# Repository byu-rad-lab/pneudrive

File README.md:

# PneuDrive Pressure Control System

This repository contains all of the designs, code, and instructions needed to create a low level pressure controller designed for pneumatically actuated robots. This pressure controller is designed to use relatively inexpensive off-the-shelf components and to favor simplicity in an effort to make it easy to understand and adapt for different applications.

Here is a [video](https://bit.ly/3QkrEqO) that is a brief overview of the system.

<!-- add picture of boards from resources folder -->

The pressure control system consists of one single-board-computer (SBC) acting as the ROS master and communicating serially with one or more Arduinos. The SBC needs to be capable of running ROS/Ubuntu (e.g. Raspberry Pi, NVIDIA Jetson, Odroid). We use the [ODROID N2+](https://www.hardkernel.com/shop/odroid-n2-with-4gbyte-ram-2/). We also provide python bindings that allow you to interact with the pressure controller without ROS.

Each Arduino performs high-rate (~1 kHz) pressure control of up to 4 chambers and transmits pressure data back to the ROS master. A high level diagram of the pressure control system can be seen in the figure below:

## Dependencies

## Installation
If the SBC is connected to the internet, the easiest way to use PneuDrive is to clone the repository directly onto the SBC. If the SBC is not connected to the internet, you can clone the repository onto another computer and then copy it over to the SBC using a tool like scp over a local network:

``` console
scp -r <path to pneudrive on computer> <username@SBC_IP_ADDRESS>:<path to desired location on SBC>
```

If you intend to use PneuDrive with ROS, just make sure the package is placed into the src directory of a ROS workspace. Once the pneudrive package in in the src directory, you can build it using ```colcon build``` from the root of the workspace.

If you intend to use PneuDrive without ROS (i.e. using the python bindings), you can place the package anywhere on the SBC. Python bindings are implemented using pybind11, so when cloning the repository, it is important to pass ```--recurse-submodules``` to git to ensure that pybind11 is cloned as well:

``` console
git clone --recurse-submodules <git url>
```

To build the bindings, you will just need to navigate to the python_bindings directory and build the bindings manually with cmake:

``` console
cd python_bindings
mkdir build
cd build
cmake ..
make
```

## How is it organized

This repository is structured as a ROS package. It is designed to be placed in a ROS workspace on the SBC used for pressure control. There are however several other directories not necessary for a ROS package:

* **pcb_design** - this directory contains all of the wiring diagrams and PCB schematics. Instructions for the population of the PCB as well as wiring the entire pressure controller are found here.
* **odroid_setup** - this directory contains all of instructions and files necessary to set up an ODROID for use as the ROS master in a pressure control system.
* **arduino_firmware** - this directory contains the instructions and code needed to program the arduinos to act as high rate pressure controllers.
* **python_bindings** - this directory contains python bindings to interact with PneuDrive independent of ROS, in a python scripting environment.

## Steps to create a pressure control system

1. Use the instructions and schematics in the **pcb_design** directory to order and assemble the necessary components to construct a PneuDrive controller PCB and several embedded PCBs.
2. Use the instructions and files in the **odroid_setup** directory to setup the SBC as the ROS master
3. Use the instructions and files in the **arduino_firmware** directory to program each arduino as a high-rate pressure controller

## Running the PneuDrive ROS Node

Once the SBC boots up it you can ssh into it with ```ssh ubuntu@192.168.0.xxx```. The username is ```ubuntu``` and the password is ```temppwd```. This process might be slightly different depending on your SBC.

Once you are logged in, you can launch the pressure control ROS node (along with a roscore) using the following command:

``` shell
ros2 launch pneudrive rs485_pressure.launch.py numjoints:=[number of joints]
```

where the ```numjoints``` command line argument is required and tells the node how many joints to look for on the serial bus. 

This creates a ROS node called "PressureController". Depending on ```numjoints```, the node will create addresses for each joint. The node then creates publishers and subscribers for every joint specified by the addresses. If the SBC cannot find all of the specified addresses, the node throw an error and shut down. If this happens, here are some common fixes:

* Make sure your wires are all connected securely and correctly.
* Make sure that each pressure control board dip switch is set to the proper address. The dip switch positions are printed on the pcb and they should match what is specified in the yaml file. For example, if I have a 3 joint arm, I would make sure that the first joint is set to 0 then the next as 1 and the last as 2, with those same addresses specified in the code. 
* Make sure you didn't flip the A+ and B- wires when wiring up the connectors. We chose to use screw terminals for ease of use, but this does make flipping wires easier if you aren't being careful. 

When the node launches, it will print out all of the joints it detected and start the node.

## Citation

If you use PneuDrive in your research, please cite the our paper:

```bibtex

 @inproceedings{
	 Johnson_Cheney_Cordon_Killpack_2024, 
	 address={San Diego, CA, USA}, 
	 title={PneuDrive: An Embedded Pressure Control System and Modeling Toolkit for Large-Scale Soft Robots}, 
	 rights={https://doi.org/10.15223/policy-029}, 
	 ISBN={9798350381818}, 
	 url={https://ieeexplore.ieee.org/document/10521958/}, 
	 DOI={10.1109/RoboSoft60065.2024.10521958}, 
	 booktitle={2024 IEEE 7th International Conference on Soft Robotics (RoboSoft)}, 
	 publisher={IEEE}, 
	 author={Johnson, Curtis C. and Cheney, Daniel G. and Cordon, Dallin L. and Killpack, Marc D.}, 
	 year={2024}, 
	 month=apr, 
	 pages={786–792}, 
	 language={en} 
 }

```

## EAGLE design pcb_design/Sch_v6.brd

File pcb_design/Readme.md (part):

# Overview

This project was made by members of the Robotics and Dynamics Lab at Brigham Young University. This directory contains all of the necessary instructions and files for the custom PCB we designed to implement pressure control for 4 different pressure chambers. This board, in combination with our beaglebone black cape, enables the use of ROS to send and receive pressure data/commands to the lower level controller located on the arduino.

These PCBs were designed using Autodesk EAGLE. The corresponding project, board, and schematic files are found in this directory, as well as the CAM outputs.

We used OSHPARK to print out PCBs. For convenience, their design rules are also included in this repo. To use them, navigate to 'Design Rules' in Eagle and click load to select the .dru file. This will load OSHPARK's manufacturing rules automatically for design rule checking.

We have also created a custom part library which includes footprints, schematics, and 3d models for each major component used in this design. To use the library, simply add the filepath of the .lbr file to Eagle's search path in the Control Panel. For more info see [here](https://www.instructables.com/Adding-a-Library-to-Eagle-CAD/).

There are two pcbs in this directory: a beaglebone black cape and the pressure control board.

Here are some renderings of the pressure control pcb:

---
# Pressure Control Board

## Bill of Materials for each Board

| Qty |  Cost  | Value                           | Device                          | Parts                                                   | Description                                 | PURCHASE_URL |
|-----|--------|---------------------------------|---------------------------------|---------------------------------------------------------|---------------------------------------------|--------------|
| 8   | $2.00  | 100nF                           | CERAMIC_CAPACITOR               | C5, C6, C7, C8, C9, C10, C11, C12                       | Ceramic capacitors for filtering            | [link](https://www.digikey.com/en/products/detail/kemet/C315C102K1R5TA7301/6562324)         |
| 4   | $1.04  | 12k                             | R-US_0204/7                     | R1, R2, R3, R4                                          | RESISTOR, American symbol                   | [link](https://www.digikey.com/en/products/detail/vishay-beyschlag-draloric-bc-components/MBB02070C1202FCT00/7351022)          |
| 4   |  $.96  | 1nF (0.1uF)                     | CERAMIC_CAPACITOR               | C1, C2, C3, C4                                          | Ceramic capacitors                          | [link](https://www.digikey.com/en/products/detail/kemet/C322C104K5R5TA7301/3726048)             |
| 1   |  $.46  | 2PIN_DIP_DS01-254-S-02BE        | 2PIN_DIP_SWITCH                 | I2C_SEL                                                 | Dip switch for selecting i2c address        | [link](https://www.digikey.com/en/products/detail/cui-devices/DS01-254-S-02BE/11310829)             |
| 2   |  $.28  | 4.7k                            | R-US_0204/7                     | R5, R6                                                  | RESISTOR, American symbol                   | [link](https://www.digikey.com/en/products/detail/vishay-beyschlag-draloric-bc-components/SFR2500004701FR500/333920)           |
| 2   | $11.90 | A4990_DUAL_MOTOR_DRIVER_CARRIER | A4990_DUAL_MOTOR_DRIVER_CARRIER | DRIVER_A, DRIVER_B                                      | A4990 Dual Motor Driver Carrier (Pololu)    | [link](https://www.pololu.com/product/2137/)              |
| 1   | $10.90 | ARDUINO_NANO_EVERY              | ARDUINO_NANO_EVERY              | NANO1                                                   | Arduino Nano Every                          | [single](https://store.arduino.cc/usa/nano-every) or [pack](https://store.arduino.cc/usa/nano-every-pack)             |
| 7   | $8.70  | PHOENIX_CONTACT_1759017         | PHOENIX_CONTACT_1759017         | 12V_IN, I2C_IN, I2C_OUT, VALVE0, VALVE1, VALVE2, VALVE3 | Crimpless connections for peripherals       | [female](https://www.digikey.com/en/products/detail/phoenix-contact/1759017/260463), [male](https://www.digikey.com/en/products/detail/phoenix-contact/1757019/260379), or [set](https://www.amazon.com/Willwin-Pitch-Pluggable-Terminal-Connectors/dp/B077GTYZVM/ref=sr_1_15?dchild=1&keywords=PCB%2BMount%2BScrew%2BTerminal%2BBlock%2C%2Bright%2Banlge%2BPlug-in%2B2-Pin%2B(2%2BPole)%2BScrew%2BTerminal%2BBlock%2BConnector%2C%2BPluggable%2BMale%2BFemale%2BPhoenix%2BType%2BConnector&qid=1619925723&s=hi&sr=1-15&th=1)             |
| 4   | $76.84 | PRESSURE_SENSOR_ABPDRNN100PGAA5 | PRESSURE_SENSOR_ABPDRNN100PGAA5 | PS0, PS1, PS2, PS3                                      | Honeywell Pressure Sensor (ABPDRNN100PGAA5) | [link](https://www.mouser.com/ProductDetail/Honeywell/ABPDRNN100PGAA5?qs=sGAEpiMZZMvhQj7WZhFIAD2P7qVC0dZ7tI11ZYAVyGqQk%2FMhVJdgGw%3D%3D)             |

NOTE: We want our pcb to be easy to service if things break. So instead of soldering parts directly to the pcb, we use [female headers](https://www.amazon.com/Qunqi-2-54mm-Straight-Connector-Arduino/dp/B07CGGSDWF/ref=sr_1_3?dchild=1&keywords=female+header+pins&qid=1587769954&sr=8-3) to plug the arduino and motor drivers in so that they can be replaced easily.

The total price per board (including printing the pcb) is about $150 (parts are $113.08 and Oshpark charges about $40 for 3 copies of the pcb). Note that there are farily significant bulk discounts for many of these parts. 

## Schematic

## Specifications and Design Notes
### I2C Design
The I2C bus on this pcb has both an IN and OUT port. The OUT port is useful for daisy chaining multiple of these pcbs, but is not required. The arduino communicates on a 5V logic level, which is incompatible with the 3.3V logic of the BBB. To remedy this, we use a bi-directional logic level shifter to make sure voltages are at the right levels for each device. The shifter is used once on the BBB cape and outputs 5V to any arudino board down the line. The logic shifter uses 10k pullup resistors on the SDA and SCL lines. According to [this](https://www.ti.com/lit/an/slva689/slva689.pdf?ts=1612978067135&ref_url=https%253A%252F%252Fwww.google.com%252F) resource, 10k is too high for our I2C line. 

The max for I2C fast mode is 400 pF according to Table 1. Since we don't have that many devices and the wires aren't super long, we assumed a bus capacitance of about 150pF. This combined with the operating voltage of 5V on fast mode gives a minimum resistance value of about 1.5k (from Fig 2) and a max resistance of about 2.5k 9 (from Fig 3). In order to get an equivalent resistance in this range with the 10k resistors in the logic shifter, we add a 2.2k resistor in parallel to get an equivalent pullup resistance of 1.8k. We measured the performance of the I2C bus with these resistors in place and observed about 380-390Hz bit rate (the 10k resistors alone work, but the bit rate was ~340Hz and the voltage level was barely reaching high). The closer the equivalent resistance is to the minimum resistance, the faster the line can transfer data at the cost of higher power consumption. 

### PCB Design Notes

* Trace widths on the board are mostly the default that eagle uses with a few exceptions. The 12V line is 80mils wide and the 5V line is 30 mils wide. The trace for the 12V line was made as as large as possible because it is a high current line. Each 2 phase driver board can deliver 0.7 amps/phase, which gives a total continuous current of up to 2.8A on each board. The driver boards can go up to 0.9A/phase, but not for long. Using [this](https://www.digikey.com/en/resources/conversion-calculators/conversion-calculator-pcb-trace-width) trace width calculator tool (with 2.8A, 1oz/ft^2, and an ambient temp of 25C) gives us an acceptably low temperature rise (5-10C) for an external trace.

* There are two ground planes in this PCB. The top plane is for the signal ground and the bottom plane is the motor power ground. This was done in an attempt to minimize noise from the motors on the analog pressure sensors. These ground are connected through the GND pins on the driver boards so that the both ground planes are connected to each other when it is running. But by only connecting the ground planes through the driver boards, it encourages any noisy currents to follow the path of least impedance (the ground plane) back to source instead of going through the signal ground. We used [this](https://www.nxp.com/docs/en/application-note/AN1259.pdf) and [this](https://electronics.stackexchange.com/questions/112508/ground-vs-power-ground) as resources as to why we chose to do this. We also did our best to separate the two areas of the board (i.e. the drivers from the pressure sensors) as much as possible without making the board too big. 

* The mounting holes are designed for M3 screws.

## Board and CAD File

See [here](https://a360.co/3wIiBnY) to see the 3d version of the board. You can download the included step file too if you want to design a case, for example.

## Things to consider for a future revision of the board

* Find a robust way to plug the pressure sensors into the board. Right now they're soldered directly to the board, but it would be convenient to be able to unplug and replace them.
* Do something with the EF pins on the driver boards. Right now they are connected to the arduino, but not doing anything with them. 
* We are using shielded cable for the i2c bus. Technically, the cable shield should be grounded somewhere. It isn't currently. Could add a screw terminal to the board to ground the bare ground wire possibly.

---
# Beaglebone Black Cape

## Bill of Materials

| Qty | Cost  | Value                      | Device                     | Package                 | Parts                                        | Description                                   | Purchase Link                                                                                                                                                                                                                                                                                                                                                                                                                                             |
|-----|-------|----------------------------|----------------------------|-------------------------|----------------------------------------------|-----------------------------------------------|-----------------------------------------------------------------------------------------------------------------------------------------------------------------------------------------------------------------------------------------------------------------------------------------------------------------------------------------------------------------------------------------------------------------------------------------------------------|
| 4   |       | 2.2k                       | R-US_0204/7                | 0204/7                  | R1, R2, R3, R4                               | RESISTOR, American symbol                     |                                                                                                                                                                                                                                                                                                                                                                                                                                                           |
| 5   | $8.70 | PHOENIX_CONTACT_1758018    | PHOENIX_CONTACT_1758018    | PHOENIX_CONTACT_1758018 | GND, I2C1_OUT, I2C2_OUT, PWR_BUT, PWR_ENABLE | Crimpless peripheral connections              | [female](https://www.digikey.com/en/products/detail/phoenix-contact/1758018/260496), [male](https://www.digikey.com/en/products/detail/phoenix-contact/1757019/260379), or [set](https://www.amazon.com/Willwin-2-Pin-5-08mm-Female-Terminal/dp/B077979RZR/ref=pd_di_sccai_3?pd_rd_w=A5pho&pf_rd_p=c9443270-b914-4430-a90b-72e3e7e784e0&pf_rd_r=5PEX8D4W251F0MR04JT6&pd_rd_r=e4559510-59fe-4a1b-9aaf-c49878303df9&pd_rd_wg=2cx5U&pd_rd_i=B077979RZR&th=1) |
| 1   | $2.50 | POLOLU_LOGIC_SHIFTERPOLOLU | POLOLU_LOGIC_SHIFTERPOLOLU | POLOLU_LOGIC_SHIFTER    | SHIFTER1                                     | Logic Level Shifter, 4-Channel, Bidirectional | [link](https://www.pololu.com/product/2595)                                                                                                                                                                                                                                                                                                                                                                                                               |

NOTE: BBB protocape ([link](https://www.adafruit.com/product/572)) was useful in prototyping. This has been replaced by our own custom pcb. 

Total cost of this board is about $50. (parts are about $10 and Oshpark charges about $40 for 3 copies of the pcb).

## Schematic

## Design Notes
 * See I2c Design above.
 * We chose to use vertical Phoenix connectors for this board because it is to be mounted inside of an enclosure and the right angle connectors take up a lot of space. 
 * The power button connection is connected to the beaglebone's power button for a hardware method to power down the beaglebone (see this [example](http://gencarelle.com/blog/2014/08/26/power-button-for-beaglebone-black/)).
 * There are two i2c buses on the BBB (technically 3, but one is used internally). There is one connector for access to each bus.
 * The power enable connection is for the estop and power relay. This is a digital ouput so that both the estop and the beaglebone can both control power while still keeping the estop software independent for safety. See the FOLLOWING DIAGRAM:
 * Ground connection is just an extra access point to BBB ground so that the power supply can be grounded together with the beaglebone.
 
# Putting it all together

## Enclosure Stuff:

* [Enclosure](https://www.amazon.com/12-2-115mm-Metal-Enclosure-Project/dp/B07G95V7YC/ref=pd_di_sccai_1?pd_rd_w=I5rdI&pf_rd_p=c9443270-b914-4430-a90b-72e3e7e784e0&pf_rd_r=7QFJZRAB7NJ2AP8N4YB6&pd_rd_r=0771ee2a-d3c7-4df1-b478-44d31392f34c&pd_rd_wg=qigFo&pd_rd_i=B07G95V7YC&th=1) on amazon fits everything nicely. 
* [Panel mount ethernet extension](https://www.adafruit.com/product/4215?gclid=Cj0KCQjw-LOEBhDCARIsABrC0TlaVVkPRgYQnkOMLTnrQEoghTae29z3SAouX9LPYDEf6-AYeaxEKM8aAt0_EALw_wcB)
* [Panel mount usb extension](https://www.adafruit.com/product/4055?gclid=Cj0KCQjw-LOEBhDCARIsABrC0Tl8-U2JYnmXrtTfUWt_J1TNg8gNP91sTYFdloDnbkfO0Z6vgGVJUYgaArRYEALw_wcB)
* [Panel mount Phoenix contact connectors](https://www.digikey.com/en/products/detail/phoenix-contact/0707248/348291?utm_adgroup=Terminal%20Blocks%20-%20Panel%20Mount&utm_source=google&utm_medium=cpc&utm_campaign=Shopping_Product_Connectors%2C%20Interconnects&utm_term=&utm_content=Terminal%20Blocks%20-%20Panel%20Mount&gclid=Cj0KCQjw-LOEBhDCARIsABrC0Tki_DSLXojhLEQjRhTL7HOXp9duJyBKhw32B4YBV-cMwi0aZF9Q28caAgXcEALw_wcB). These are used for the Estop in, i2c out, and power out connections.
* [Panel mount power button](https://www.adafruit.com/product/1505)
* [Power connection module](https://www.amazon.com/gp/product/B082ZFRV1B/ref=ox_sc_act_title_3?smid=A3PXX08VVBPF5M&psc=1)

TODO: add cad stuff of panel and template printout for cutting.

## Additional random stuff:

* I2C communication wires. We used this[here](https://www.mcmaster.com/8128T1/) because it is double shielded and rated for up to 35 Mbps data rates (we are at 400kbps).
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
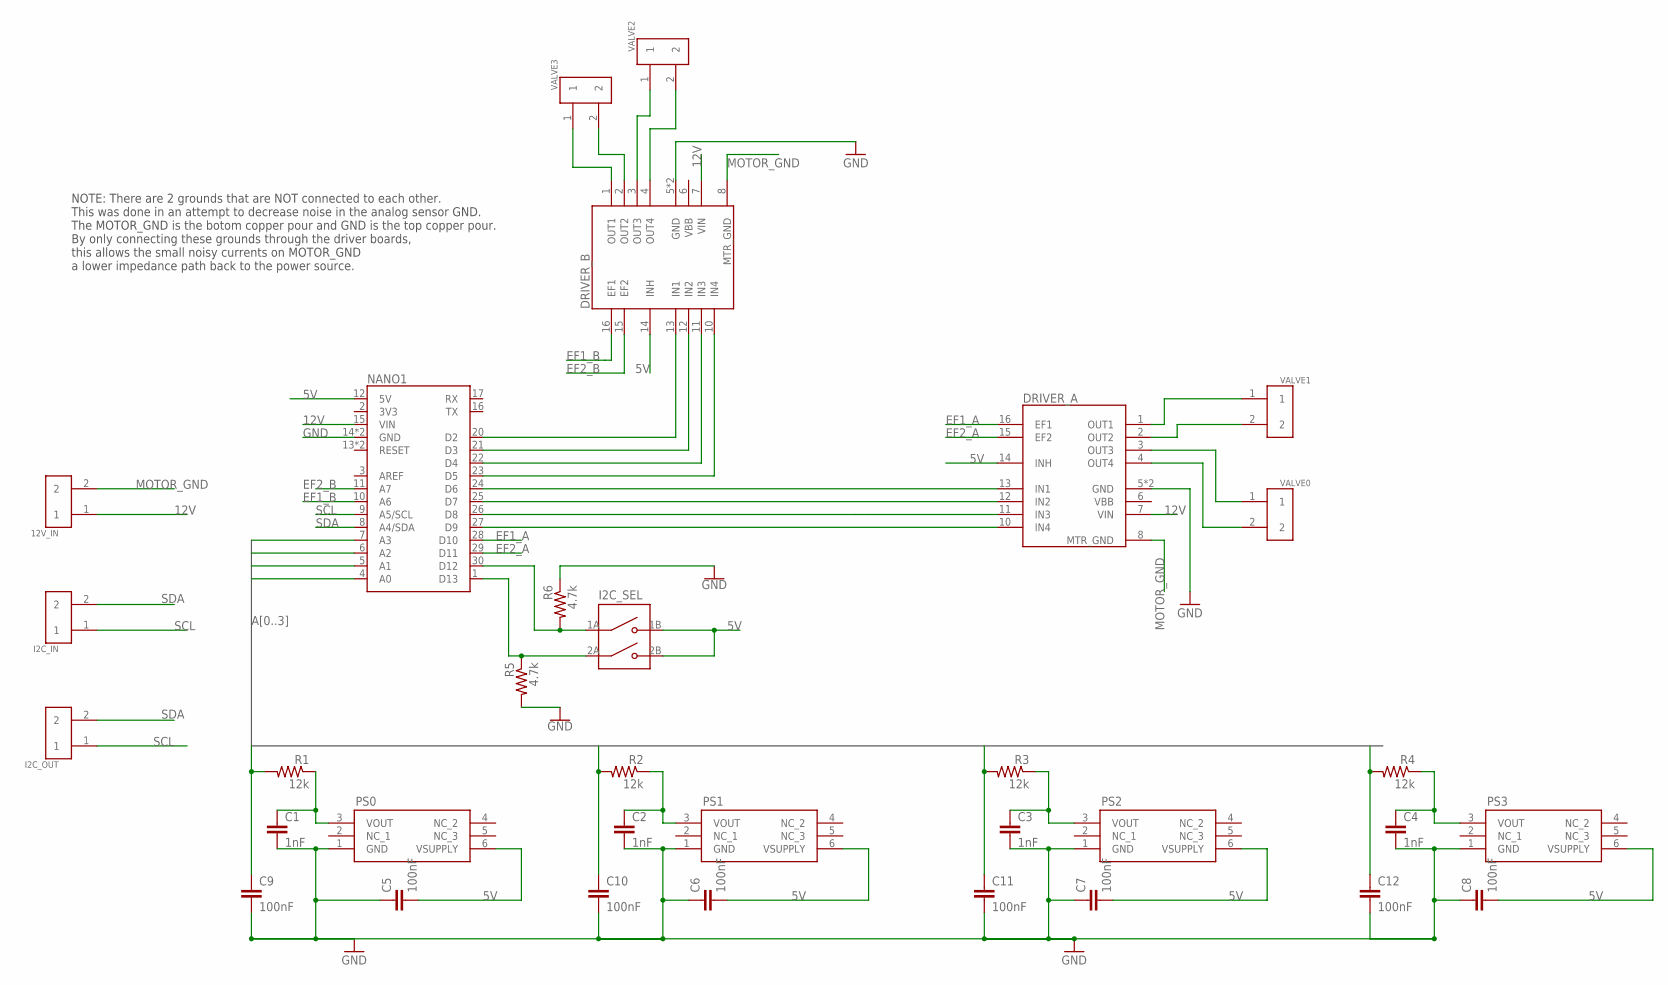
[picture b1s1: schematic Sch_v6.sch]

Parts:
12V_IN: PHOENIX_CONTACT_1759017
C1, C2, C3, C4: 1nF; CERAMIC_CAPACITOR
C5, C6, C7, C8, C9, C10, C11, C12: 100nF; CERAMIC_CAPACITOR
DRIVER_A: A4990_DUAL_MOTOR_DRIVER_CARRIER
DRIVER_B: A4990_DUAL_MOTOR_DRIVER_CARRIER
I2C_IN, I2C_OUT: PHOENIX_CONTACT_1759017
I2C_SEL: 2PIN_DIP_DS01-254-S-02BE
NANO1: ARDUINO_NANO_EVERY
PS0, PS1, PS2, PS3: PRESSURE_SENSOR_ABPDRNN100PGAA5
R1, R2, R3, R4: 12k; 0204/7
R5, R6: 4.7k; 0204/7
VALVE0, VALVE1, VALVE2, VALVE3: PHOENIX_CONTACT_1759017

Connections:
5V: C5.2, C6.2, C7.2, C8.2, DRIVER_A.14 (INH), DRIVER_B.14 (INH), I2C_SEL.1B (NO1), I2C_SEL.2B (NO2), NANO1.12 (5V), PS0.6 (VSUPPLY), PS1.6 (VSUPPLY), PS2.6 (VSUPPLY), PS3.6 (VSUPPLY)
12V: 12V_IN.1, DRIVER_A.7 (VIN), DRIVER_B.7 (VIN), NANO1.15 (VIN)
A0: C9.1, NANO1.4 (A0), R1.2
A1: C10.1, NANO1.5 (A1), R2.2
A2: C11.1, NANO1.6 (A2), R3.2
A3: C12.1, NANO1.7 (A3), R4.2
D2: DRIVER_B.13 (IN1), NANO1.20 (D2)
D3: DRIVER_B.12 (IN2), NANO1.21 (D3)
D4: DRIVER_B.11 (IN3), NANO1.22 (D4)
D5: DRIVER_B.10 (IN4), NANO1.23 (D5)
D6: DRIVER_A.13 (IN1), NANO1.24 (D6)
D7: DRIVER_A.12 (IN2), NANO1.25 (D7)
D8: DRIVER_A.11 (IN3), NANO1.26 (D8)
D9: DRIVER_A.10 (IN4), NANO1.27 (D9)
EF1_A: DRIVER_A.16 (EF1), NANO1.28 (D10)
EF1_B: DRIVER_B.16 (EF1), NANO1.10 (A6)
EF2_A: DRIVER_A.15 (EF2), NANO1.29 (D11)
EF2_B: DRIVER_B.15 (EF2), NANO1.11 (A7)
GND: C1.2, C2.2, C3.2, C4.2, C5.1, C6.1, C7.1, C8.1, C9.2, C10.2, C11.2, C12.2, DRIVER_A.5 (GND), DRIVER_A.9 (GND), DRIVER_B.5 (GND), DRIVER_B.9 (GND), NANO1.14 (GND), NANO1.19 (GND), PS0.1 (GND), PS1.1 (GND), PS2.1 (GND), PS3.1 (GND), R5.2, R6.1
MOTOR_GND: 12V_IN.2, DRIVER_A.8 (MTR_GND), DRIVER_B.8 (MTR_GND)
unnamed: C1.1, PS0.3 (VOUT), R1.1
unnamed: C2.1, PS1.3 (VOUT), R2.1
unnamed: C3.1, PS2.3 (VOUT), R3.1
unnamed: C4.1, PS3.3 (VOUT), R4.1
unnamed: DRIVER_A.2 (OUT2), VALVE1.2
unnamed: DRIVER_A.1 (OUT1), VALVE1.1
unnamed: DRIVER_A.3 (OUT3), VALVE0.1
unnamed: DRIVER_A.4 (OUT4), VALVE0.2
unnamed: DRIVER_B.1 (OUT1), VALVE3.1
unnamed: DRIVER_B.2 (OUT2), VALVE3.2
unnamed: DRIVER_B.3 (OUT3), VALVE2.1
unnamed: DRIVER_B.4 (OUT4), VALVE2.2
unnamed: I2C_SEL.1A (COM1), NANO1.30 (D12), R6.2
unnamed: I2C_SEL.2A (COM2), NANO1.1 (D13), R5.1
SCL: I2C_IN.1, I2C_OUT.1, NANO1.9 (A5/SCL)
SDA: I2C_IN.2, I2C_OUT.2, NANO1.8 (A4/SDA)

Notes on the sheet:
NOTE: There are 2 grounds that are NOT connected to each other. This was done in an attempt to decrease noise in the analog sensor GND. The MOTOR_GND is the botom copper pour and GND is the top copper pour. By only connecting these grounds through the driver boards, this allows the small noisy curr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

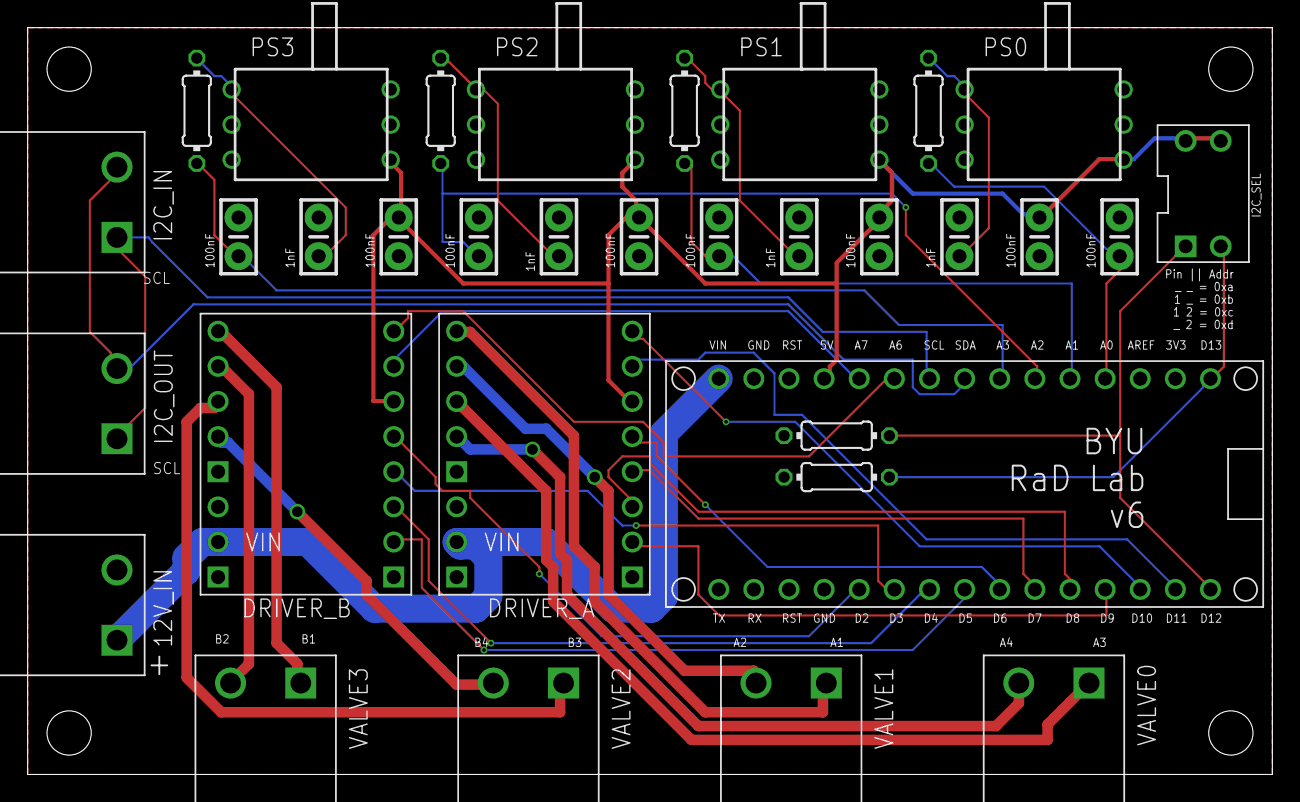
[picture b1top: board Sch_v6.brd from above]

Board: 2 copper layers, 90.0 x 54.0 mm, 33 parts (0 on the bottom side), 36 nets.

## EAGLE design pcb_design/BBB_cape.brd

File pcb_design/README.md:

This directory contains everything you need to order and assemble the PCBs needed for PneuDrive. 

# PnueDrive Controller Board
### Design Files
1. All design files (Bill of Materials, 3d step file, .sch, .brd, and a pdf of the schematic) are located in PnueDrive-Controllerv1.2-Designs.zip.

### Ordering PCB
1. Any PCB manufacturer can be used, but we have used JLCPCB in the past. Go to their [website](https://jlcpcb.com/), click upload gerber file, and upload pneudrive_controllerv1.2_gerbers.zip. After processing, it should say "Detected 4 layer board of 65x31mm(2.56x1.22 inches) ."
2. Every manufacturing option can remain default except for the following: **Remove Order Number: Specify a Location**
3. If you want, you can order a stencil to make soldering the SMT components easier. We have not done this since there are only 1 or 2 controller boards that need to be assembled.

### Ordering Components
1. The Bill of Materials (BoM) PneuDrive BoM - Controllerv1.2.pdf. The BoM contains links to purchase components, descriptions, and part numbers. The total price as of 2023 is $5.87 USD.
2. You will also need female headers to plug things into and the logic level shifter from pololu.

### Assembly
1. Solder the SMT components to the board before any of the through hole components. This is because the through hole components will get in the way of the hot air rework station. [Here](https://www.youtube.com/watch?v=fYInlAmPnGo&pp=ygUWc210IHNvbGRlcmluZyB0dXRvcmlhbA%3D%3D) is a good tutorial on how to do SMT soldering.

# PneuDrive Embedded Board

### Design Files
1. All design files (Bill of Materials, 3d step file, .sch, .brd, and a pdf of the schematic) are located in PneuDrive-Embeddedv1.2-Designs.zip.

### Ordering PCB
1.  Go to their [website](https://jlcpcb.com/), click upload gerber file, and upload pneudrive_embeddedv1.2_gerbers.zip After processing, it should say "Detected 4 layer board of 75x69mm(2.95x2.72 inches)."
2.  Every option can remain default except for the following: **Remove Order Number: Specify a Location**
3.  Order Stencil together with PCB. This costs extra, but since the embedded boards typically are assembled in volume, it is worth it.
4.  All the stencil options can stay default except the following: **Stencil Side: Bottom**

### Ordering Components
1. The Bill of Materials (BoM) PneuDrive BoM - Embeddedv1.2.pdf. The BoM contains links to purchase components, descriptions, and part numbers. The total price as of 2023 is $156.74 USD.
2. You will also need female headers to plug things into and the a4990 motor driver breakouts from pololu.

### Assembly
1. Solder the SMT components on the bottom before any of the through hole components. This is because the through hole components will get in the way of the hot air rework station. [Here](https://www.youtube.com/watch?v=fYInlAmPnGo&pp=ygUWc210IHNvbGRlcmluZyB0dXRvcmlhbA%3D%3D) is a good tutorial on how to do SMT soldering.

# Consumables

For assembly, we used the following:
*  [Solder Paste](https://www.amazon.com/Wonderway-Soldering-Electronics-CELLPHONE-Repairing/dp/B0BLSJQPR6/ref=sr_1_6?crid=6NIL0QUJVAGM&keywords=solder+paste&qid=1697561173&sprefix=solder+paste%2Caps%2C127&sr=8-6) ~$15 USD
*  [Flux](https://www.amazon.com/Smooth-Flow-No-Clean-syringe-plunger/dp/B08KJRCYRH/ref=sr_1_1?crid=447AJ25QBNVN&keywords=chip+quik+nc191&qid=1697561249&sprefix=chip+quik+nc191%2Caps%2C107&sr=8-1) ~$15 USD
*  [Solder Wire](https://www.amazon.com/Dia0-032in-0-11lb-Precision-Electronics-Soldering/dp/B07Q167J98/ref=sr_1_5?crid=2V5IWMRTC525D&keywords=solder+lead+free&qid=1697561457&sprefix=solder+lead+free%2Caps%2C109&sr=8-5) ~$10 USD

# Tools
You'll need
* A soldering iron
* A hot air rework station (for SMT components)

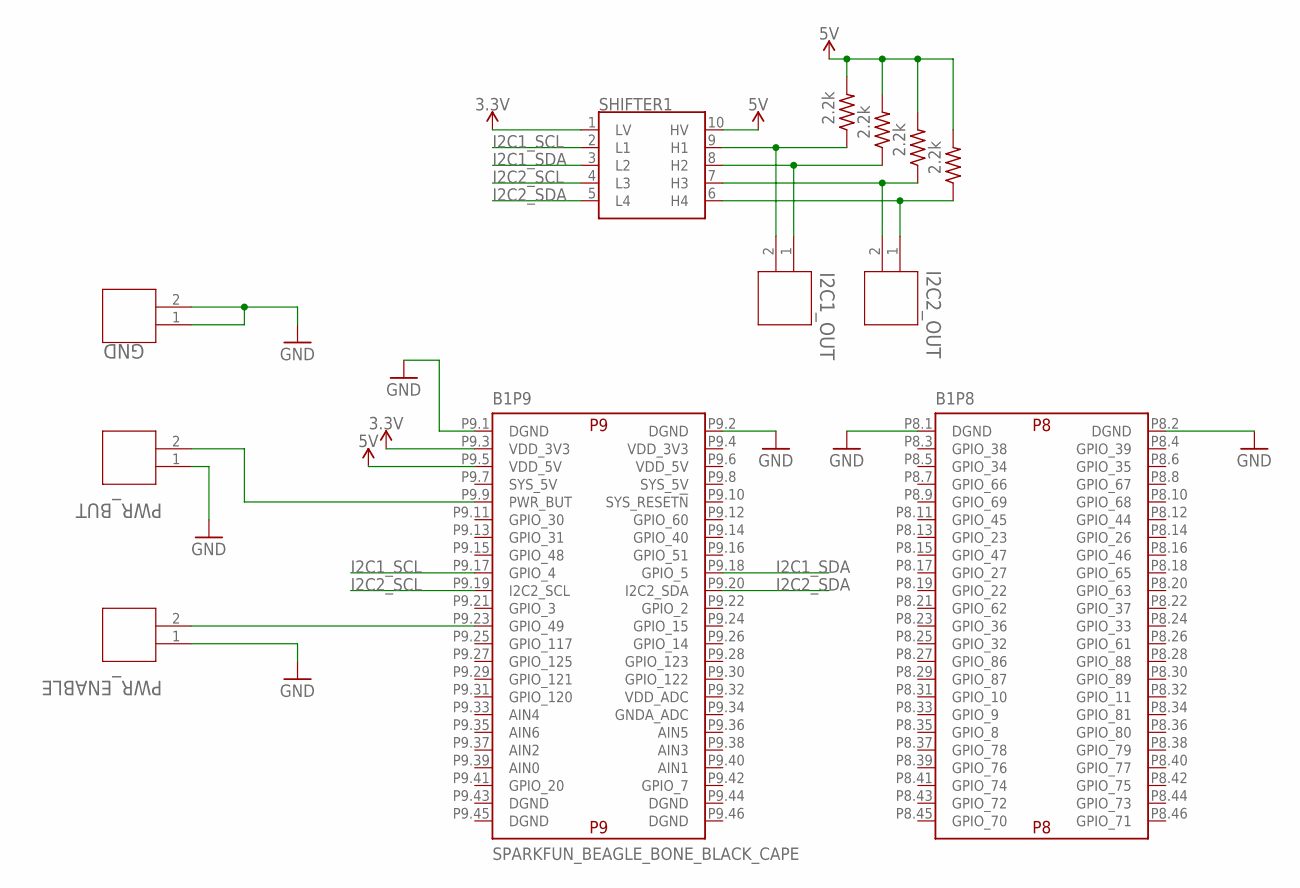
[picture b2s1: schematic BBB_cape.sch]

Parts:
B1: SPARKFUN_BEAGLE_BONE_BLACK_CAPE; BEAGLE_BONE_BLACK_CAPE
GND: PHOENIX_CONTACT_1758018
I2C1_OUT, I2C2_OUT: PHOENIX_CONTACT_1758018
PWR_BUT: PHOENIX_CONTACT_1758018
PWR_ENABLE: PHOENIX_CONTACT_1758018
R1, R2, R3, R4: 2.2k; 0204/7
SHIFTER1: POLOLU_LOGIC_SHIFTERPOLOLU; POLOLU_LOGIC_SHIFTER

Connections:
3.3V: B1.P9.3 (VDD_3V3), SHIFTER1.1 (LV)
5V: B1.P9.5 (VDD_5V), R1.2, R2.2, R3.2, R4.2, SHIFTER1.10 (HV)
GND: B1.P8.1 (DGND), B1.P8.2 (DGND), B1.P9.1 (DGND), B1.P9.2 (DGND), GND.1, GND.2, PWR_BUT.1, PWR_ENABLE.1
I2C1_SCL: B1.P9.17 (GPIO_4), SHIFTER1.2 (L1)
I2C1_SDA: B1.P9.18 (GPIO_5), SHIFTER1.3 (L2)
I2C2_SCL: B1.P9.19 (I2C2_SCL), SHIFTER1.4 (L3)
I2C2_SDA: B1.P9.20 (I2C2_SDA), SHIFTER1.5 (L4)
unnamed: I2C1_OUT.2, R1.1, SHIFTER1.9 (H1)
unnamed: I2C1_OUT.1, R2.1, SHIFTER1.8 (H2)
unnamed: I2C2_OUT.2, R3.1, SHIFTER1.7 (H3)
unnamed: I2C2_OUT.1, R4.1, SHIFTER1.6 (H4)
unnamed: B1.P9.23 (GPIO_49), PWR_ENABLE.2
unnamed: B1.P9.9 (PWR_BUT), PWR_BUT.2

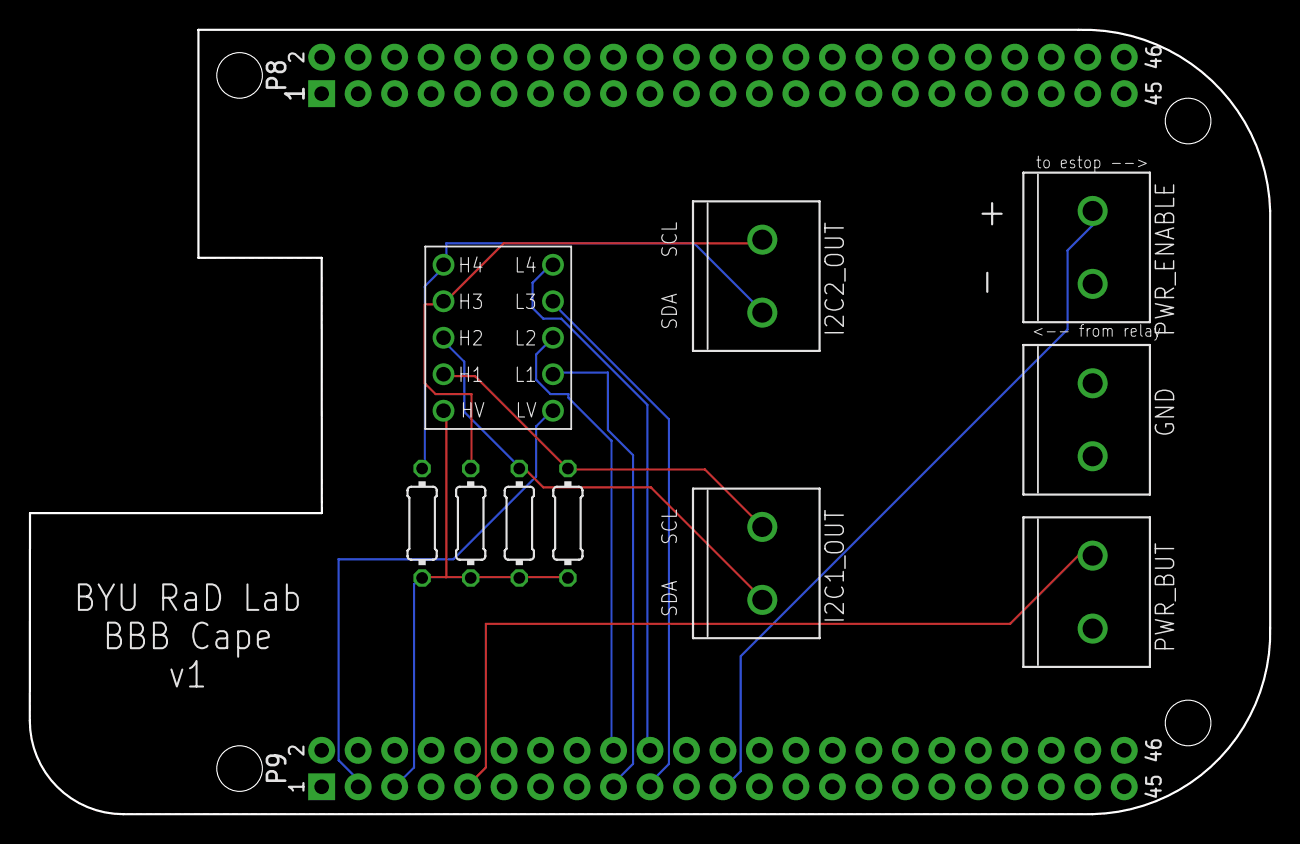
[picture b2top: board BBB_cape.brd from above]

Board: 2 copper layers, 86.4 x 54.6 mm, 11 parts (0 on the bottom side), 13 nets.

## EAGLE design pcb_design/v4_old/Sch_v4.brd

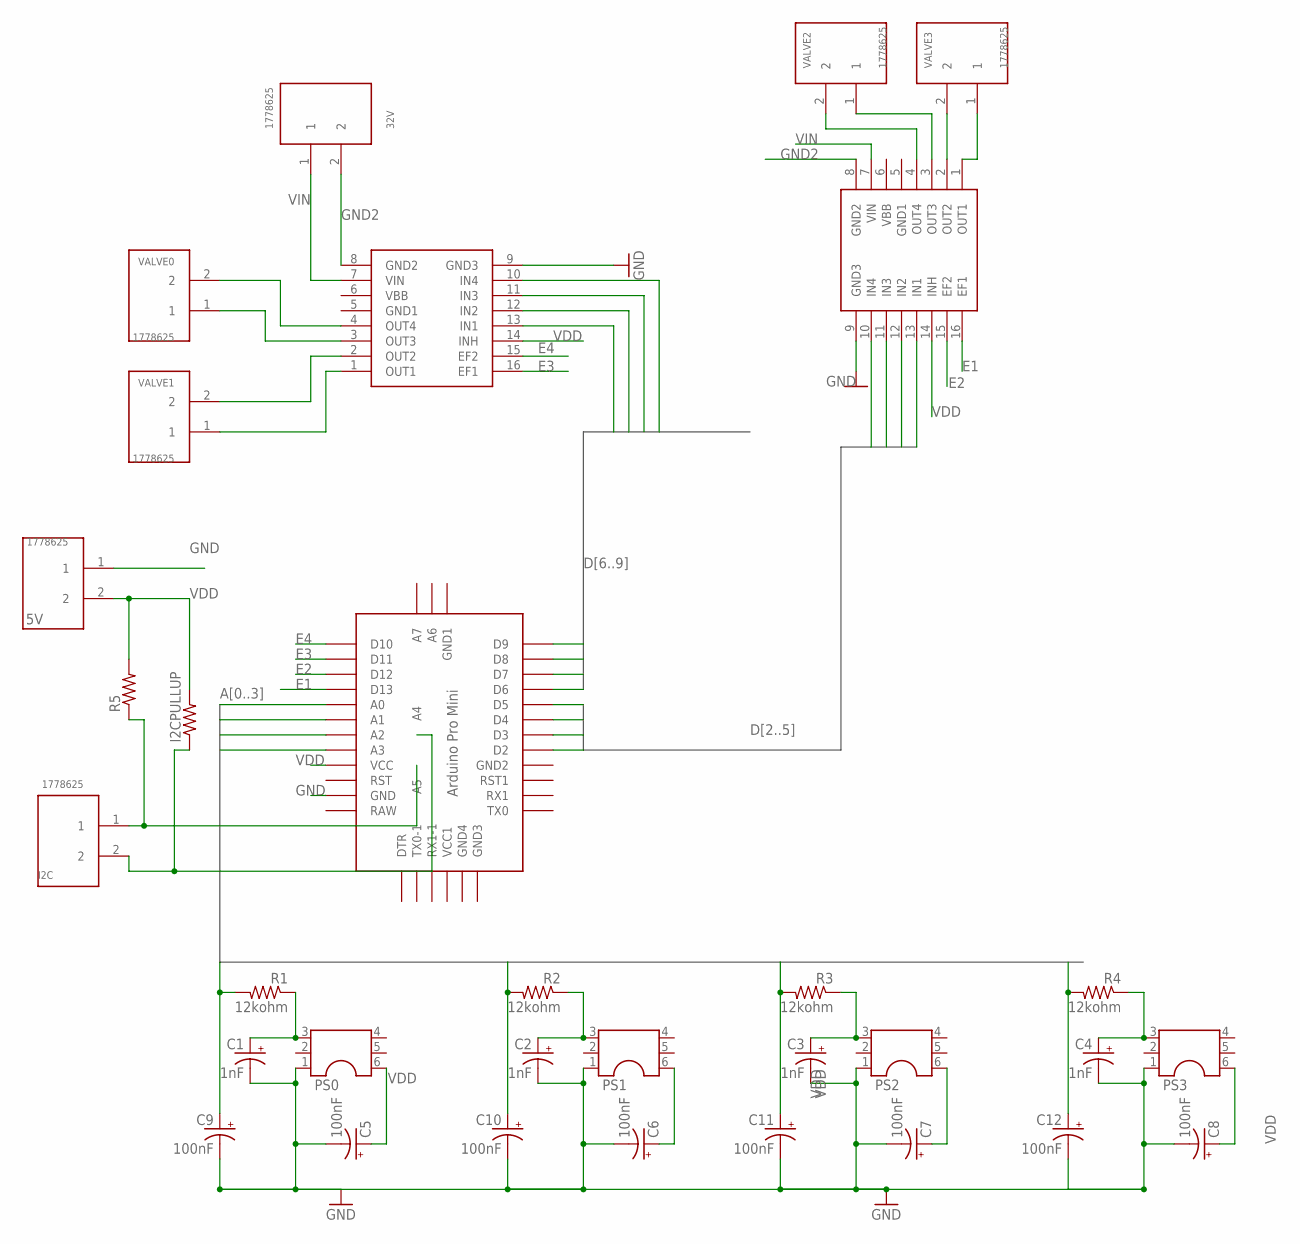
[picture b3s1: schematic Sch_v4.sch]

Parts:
5V, 32V: 1778625
C1, C2, C3, C4: 1nF; E2,5-5
C5, C6, C7, C8, C9, C10, C11, C12: 100nF; E2,5-5
I2C: 1778625
I2CPULLUP: R-US_0204/7; 0204/7
PS0, PS1, PS2, PS3: ABPDRNN100PGAA5
R1, R2, R3, R4: 12kohm; 0204/7
R5: R-US_0204/7; 0204/7
U$1: ABK-PRO-MINI
U$2, U$3: A4990
VALVE0, VALVE1, VALVE2, VALVE3: 1778625

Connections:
A0: C9.+, R1.2, U$1.A0
A1: C10.+, R2.2, U$1.A1
A2: C11.+, R3.2, U$1.A2
A3: C12.+, R4.2, U$1.A3
D2: U$1.D2, U$3.13 (IN1)
D3: U$1.D3, U$3.12 (IN2)
D4: U$1.D4, U$3.11 (IN3)
D5: U$1.D5, U$3.10 (IN4)
D6: U$1.D6, U$2.13 (IN1)
D7: U$1.D7, U$2.12 (IN2)
D8: U$1.D8, U$2.11 (IN3)
D9: U$1.D9, U$2.10 (IN4)
E1: U$1.D13, U$3.16 (EF1)
E2: U$1.D12, U$3.15 (EF2)
E3: U$1.D11, U$2.16 (EF1)
E4: U$1.D10, U$2.15 (EF2)
GND: 5V.1, C1.-, C2.-, C3.-, C4.-, C5.-, C6.-, C7.-, C8.-, C9.-, C10.-, C11.-, C12.-, PS0.1, PS1.1, PS2.1, PS3.1, U$1.GND, U$2.9 (GND3), U$3.9 (GND3)
GND2: 32V.2, U$2.8 (GND2), U$3.8 (GND2)
unnamed: C1.+, PS0.3, R1.1
unnamed: C2.+, PS1.3, R2.1
unnamed: C3.+, PS2.3, R3.1
unnamed: C4.+, PS3.3, R4.1
unnamed: U$2.2 (OUT2), VALVE1.2
unnamed: U$2.1 (OUT1), VALVE1.1
unnamed: U$2.3 (OUT3), VALVE0.1
unnamed: U$2.4 (OUT4), VALVE0.2
unnamed: U$3.1 (OUT1), VALVE3.1
unnamed: U$3.2 (OUT2), VALVE3.2
unnamed: U$3.3 (OUT3), VALVE2.1
unnamed: U$3.4 (OUT4), VALVE2.2
unnamed: I2C.1, R5.1, U$1.A5
VDD: 5V.2, C5.+, C6.+, C7.+, C8.+, I2C.2, I2CPULLUP.1, I2CPULLUP.2, PS0.6, PS1.6, PS2.6, PS3.6, R5.2, U$1.A4, U$1.VCC, U$2.14 (INH), U$3.14 (INH)
VIN: 32V.1, U$2.7 (VIN), U$3.7 (VIN)

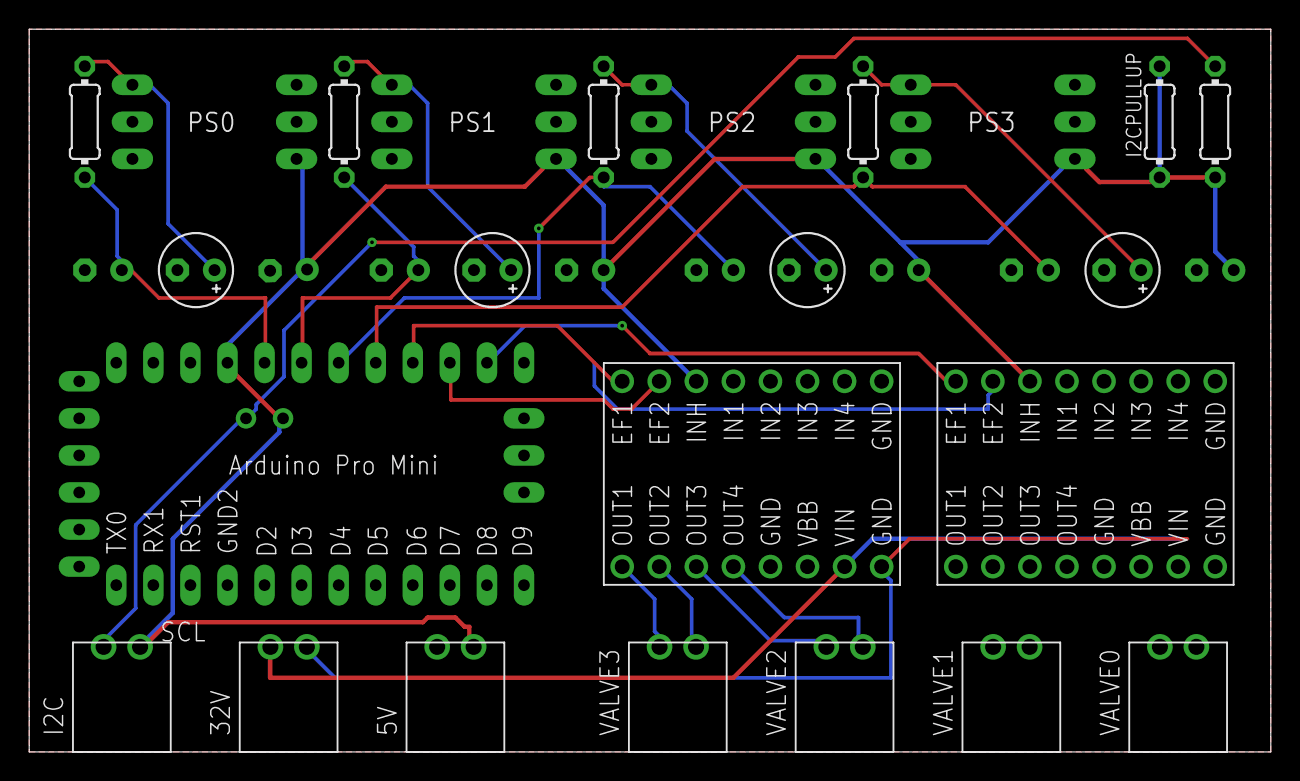
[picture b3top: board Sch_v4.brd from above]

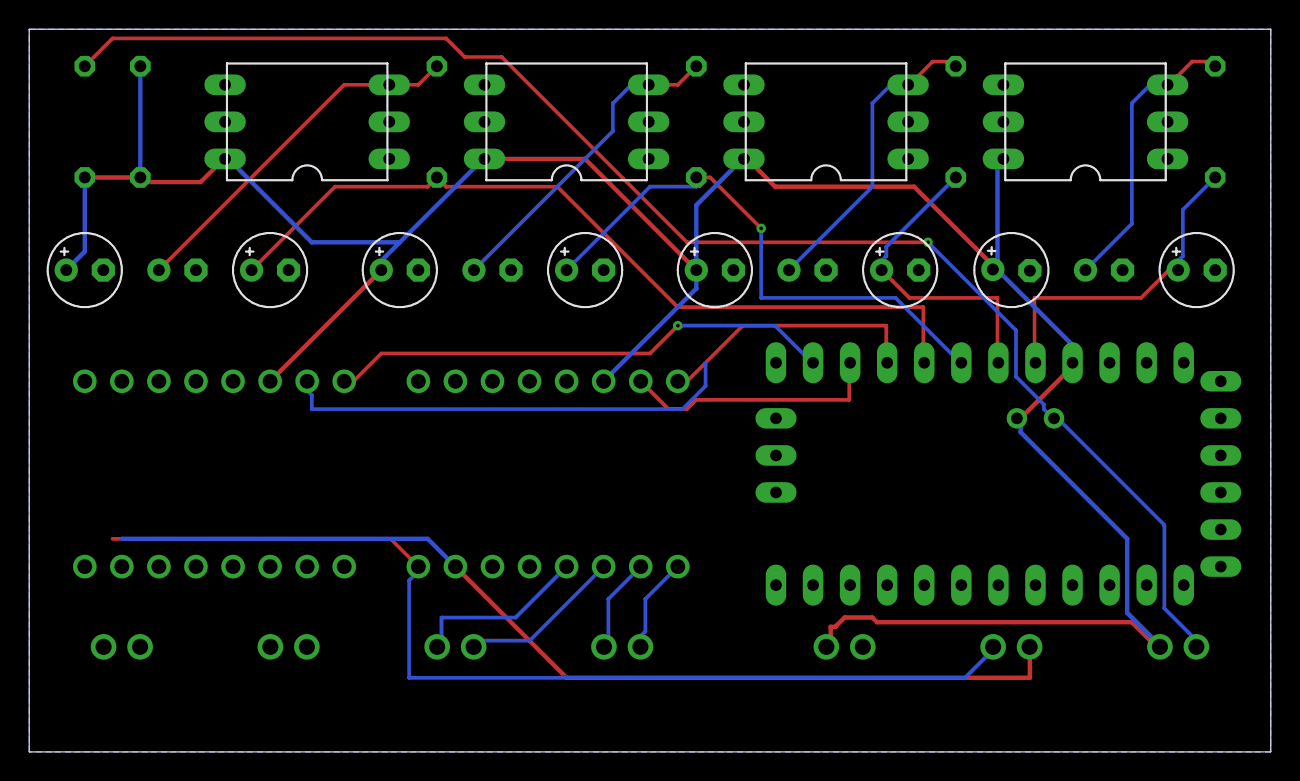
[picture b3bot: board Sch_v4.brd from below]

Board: 2 copper layers, 85.1 x 49.5 mm, 32 parts (12 on the bottom side), 33 nets.

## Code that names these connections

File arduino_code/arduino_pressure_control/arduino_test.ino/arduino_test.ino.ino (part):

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// motor driver error pins
const int EF1_A = 10;
const int EF2_A = 11;
const int EF1_B = 20;
const int EF2_B = 21;

// conversion factor from psi to kpa (ie kpa = psi * PSI2KPA)
double const PSI2KPA = 6.8947572932;
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  }

  //set up fault pins, input pullup bc no external pull is used.
  pinMode(EF1_A, INPUT_PULLUP);
  pinMode(EF2_A, INPUT_PULLUP);
  pinMode(EF1_B, INPUT_PULLUP);
  pinMode(EF2_B, INPUT_PULLUP);

  // check valve control connections
  Serial.print("Venting each valve control connection for 10 seconds. Use a multimeter to check voltages on each connector. Make sure 12V supply is connected");
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
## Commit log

2020-04-16 Initial commit for the byu_pressure_control ros package. Just setting up structure.
2020-04-16 Changes to be committed: new file: pcb_design/pcb_schematics.pdf
2020-04-16 README.md edited online with Bitbucket
2020-04-16 Changes to be committed: new file: pressure_control_system_diagram.png
2020-04-16 Added picture to Readme
2020-04-16 BBSetup.md created online with Bitbucket
2020-04-16 beaglebone_setup/BBSetup.md edited online with Bitbucket
2020-04-22 Changes to be committed: modified: uEnv.txt
2020-04-22 copied things from the good BB
2020-04-22 Changes to be committed: new file: bb_install_script.sh
2020-04-22 Trying out a new install script
2020-04-22 Fixed CMakeLists.txt and package.xml to be the correct package name
2020-04-22 Changes to be committed: new file: I2CDevice.cpp new file: I2CDevice.h
2020-04-22 Added setting ip on startup and launching imu and pressure control on boot Changes to be committed: modified: bb_install_script.sh new file: set_ip_on_startup
2020-04-22 Changes to be committed: modified: bb_install_script.sh
2020-04-22 fixed launch files
2020-04-22 perfecting install script on the beaglebone itself
2020-04-22 I think this install script works, but only for pressure control, not IMU publishing too
2020-04-22 stil trying to figure out robot_upstart via an install script...
2020-04-23 I am starting to make the BeagleBone code more object oriented. I fully expect this commit to break things.
2020-04-23 Things build, but haven't tested on hardware yet. Changes to be committed: modified: src/I2CDevice.h modified: src/PressureController.cpp modified: src/PressureController.h modified: src/i2c_pressure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
2020-04-23 i2c_pressure_control.cpp works to detect multiple i2c devices and make different publishers and subscribers for each. Changes to be committed: modified: CMakeLists.txt modified: src/I2CDevice.cpp mod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
2020-04-24 Pressure controller accepts multiple nodes based on how many are there when starting. I have verified that the Arduino is receiving pressure commands I have verified that the BBB is getting pressures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
2020-04-24 Readme.md created online with Bitbucket
2020-05-13 This arduino code ran the real grub and it worked well.
2020-05-26 Committing the Arduino code after changing the move_valve function to take in a positive or negative number
2020-06-09 Made the IMUPublisher like the PressureController in structure and format Changes to be committed: modified: CMakeLists.txt new file: src/IMUPublisher.cpp new file: src/IMUPublisher.h modified: src/i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
2020-06-09 Changes to be committed: new file: arduino_imu_pose_estimation.ino
2020-06-09 IMU pose estimation works reasonably well. Need to calibrate IMUs and try Changes to be committed: modified: arduino_code/arduino_imu_pose_estimation/arduino_imu_pose_estimation.ino modified: arduino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
2020-06-09 Commit from beaglebone. IMUPublisher works well. Changes to be committed: modified: src/IMUPublisher.cpp modified: src/i2c_imu_publisher.cpp
2020-06-10 Made calibration script for IMUs and IMU pose estimation works well.
2020-06-10 Added visualization for arduino IMU pose estimation Changes to be committed: new file: Visualizer.pde
2020-06-18 Changes to be committed: deleted: arduino_imu_pose_estimation/Visualizer.pde modified: arduino_imu_pose_estimation/arduino_imu_pose_estimation.ino
2020-06-19 Added calibration for IMUs A through D
2020-06-30 Phil's final commit of imu pose estimation from work computer. modified: ../arduino_code/arduino_imu_pose_estimation/arduino_imu_pose_estimation.ino
2020-06-30 Changes to be committed: modified: CMakeLists.txt deleted: arduino_code/arduino_imu_calibration/arduino_imu_calibration.ino deleted: arduino_code/arduino_imu_pose_estimation/arduino_imu_pose_estimati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
2020-06-30 Added PCB files to pcb_design folder
2020-10-06 arduino_pressure_control.ino edited online with Bitbucket
2020-11-21 Updated connector info in README
2020-11-22 Created folder for older versions of the PCB
2020-11-22 Sch_v3.pro edited online with Bitbucket
2020-11-22 pcb_design/Sch_v3.sch edited online with Bitbucket
2020-11-22 add startup_features script
2020-11-22 beaglebone_setup/startup_features edited online with Bitbucket
2020-11-23 Updated PCB files
2020-11-23 Readme.md edited
2020-11-24 Add PCB silkscreen image
2020-11-24 Add labeled PCB image
2020-11-24 Edit file path for picture
2020-11-24 Copy image to main directory
2020-12-18 added some debugging things with ros logging
2021-01-25 updated to v5. Cleaned up schematic a bit. Still need to fix I2C, flipped pins, etc.
2021-01-26 Fixed I2C traces, changed power on arduino from VCC pin to Raw, updated silkscreen
2021-01-30 adding M3 mounting holes with no solder mask
2021-02-09 added byu parts library
2021-02-09 added library dir
2021-02-16 commiting recent work
2021-02-16 board routed
2021-02-16 added BBB cape beginning
2021-02-16 final version of pcb I think
2021-02-17 added dip switch. autorouting completed
2021-02-17 fixed small bug
2021-02-17 fixed another bug
2021-02-18 adding library and design rules
2021-02-19 adding new schematic pic
2021-02-24 last few changes and CAM outputs generated
2021-02-24 pcb_design/pcb_schematics.pdf edited online with Bitbucket
2021-02-24 pcb_design/pcb_top.png edited online with Bitbucket
2021-02-24 deleted step file bc we don't need it here
2021-02-24 pushing arduino work and oshpark zip file
2021-02-26 pushing arduino code
2021-02-26 debugging automatic calibration of sensors
2021-03-12 all 4 pressures are being sent across ROS sucessfully
2021-03-17 pushing from beaglebone. new pcb working, callback not working - Curtis
2021-03-23 PI control working on hardware
2021-03-23 PI control working -Curtis
2021-03-24 Added Trapezoidal integration and a dirty derivative. Check comments for TODO: messages
2021-03-25 fixing some bugs, still have some work to do
2021-03-30 Proportional control bugs fixed. most consistent version yet
2021-05-07 added v6 with better connectors and some small drill changes
2021-05-10 removed old files and updated with CAM files for both pcbs.
2021-05-11 added submodule and changing messages to match simulation
2021-05-12 fixing submodule
2021-05-12 updated submodule and msg types
2021-05-12 updated formatting
2021-05-17 added checking for expected i2c_devices
2021-05-28 bb_install_script.sh
2021-05-29 fixed spacing in bbb cape
2021-06-01 updated files and cams
2021-06-01 added pics of new pcb
2021-06-01 added step file
2021-06-04 added arduino test script and cleaned up stuff in control script.
2021-06-14 fixed rosparam not loading bug
2021-06-14 fixed topic numbering bug
2021-06-15 added valve library interface for much cleaner code.
2021-06-15 commented out fault stuff
2021-06-24 added library for valves. Pressure control working.
2021-06-25 cleaning up
2021-06-25 fixed string bug
2021-06-25 removed submodule
2021-06-25 fixed dependency on radmsg
2021-07-20 added ability to switch between 8bit and 16 bit precision. Also upgraded to ROS noetic.
2021-07-20 added ability on arduino to switch between 8bit and 16bit precision
2021-07-20 officially working again
2022-03-01 fixing some small stuff
2022-03-02 adding pictures
2022-05-26 changed Pressure command subscribers to 1 queue size with tcpnodelay.
2022-06-17 updating proportional controller to be more stable
2022-06-17 added command line arg for numjoints to easily switch between configurations
2022-06-17 updated launch instructions
2022-06-17 tuned pressure controller on arm
2023-04-20 cleanup
2023-07-31 Adding odroid + arduino code for sending RS485 serial comms
2023-08-01 Updated RS485 code with microsecond delays
2023-08-01 receive arduino address in read serial
2023-08-16 arduino_code.ino edited online with Bitbucket. Working call response. Needs to be integrated into i2c code and cleaned up
2023-08-16 sendSerial.c edited online with Bitbucket. updated odroid code to block until 9 bytes are received in response.
2023-08-23 Removed i2c related code, adjusted PressureController.cpp with code from RS485_code and updated arduino_pressure_control
2023-08-31 working rs485 address function
2023-08-31 Added check_devices functionality
2023-08-31 Made compatible with RS485 protocol
2023-09-01 platform io push
2023-09-01 forgot gitignore
2023-09-01 fixing addresses on arduino
2023-09-06 I think handling incoming data is working now
2023-09-06 adding odroid code that is working
2023-09-06 odroid config files
2023-09-06 and cmakelists
2023-09-06 i think everything is working at 500 Hz publishing over ROS.
2023-09-07 fixed byte issues
2023-09-07 new address working with 1 device
2023-09-07 fixed byte bug
2023-09-07 pressure data publishing working from arduino sensors
2023-09-07 now arduinos receive ROS commands
2023-09-11 addding packetized reset after responding to avoid buffer overflow
2023-09-11 working code with timeouts
2023-09-11 code cleanup
2023-09-18 cleaned up code and working again by changing to steady_clock from ros::time
2023-09-18 added checks for erroneous bytes that are clearly out of range.
2023-09-18 extra 0xFF gone...?
2023-09-19 functioning control! woop woop. added digital 1st order filter.
2023-09-19 tuned PID, as agressive as possible without jittering
2023-09-20 adding documentation
2023-09-20 code clean up
2023-09-20 fix accidental push cleanup
2023-09-20 remove old stuff
2023-09-20 fixing code to build after rename
2023-10-05 adding git ignore
2023-10-05 adding pybind11 as submodule for python api
2023-10-05 fixed python bindings
2023-10-05 removed old pybind stuff
2023-10-06 added raising errors instead of just print statements
2023-10-17 adding docs to repo
2023-10-17 docs
2024-02-13 910 ohm resistor change updated in BOM
2024-02-14 updating bom to get right resistor after version mix up
2024-02-14 updating docs and design files
2024-02-16 turning off debug mode
2024-02-16 adding catkin_ignore
2024-02-16 adding namespace to topic names for multiple robots
2024-02-27 added software LPF with fast fixed point math
2024-02-27 updated to long type to avoid overflow bug in LPF.
2024-05-07 adding derivative control and tuning for new joints.
2024-05-07 detuned a bit for smoother performance. Still little SS error.
2024-05-08 fixed bug where arduino continuously tries to vent before pneudrive is running. Caused excessive heat up on hardware
2024-05-09 improving stats tracking for communication quality.
2024-05-15 package.xml edited online with Bitbucket
2024-05-16 tuned controller on baloo's arms.
2024-05-17 fixed big jump on startup bug
2024-05-20 adding some error checking on arduino side.
2024-06-03 added official citation
2024-06-05 fixing namespace integration
2024-06-05 updated to get parameter relative to node namespace.
2024-06-26 Testing new branch
2024-06-27 Updated package.xml to include ROS2 dependencies
2024-07-02 Updated CMakeLists.txt to fit ROS 2 configurations
2024-07-02 Changed PressureController.hpp to match ROS 2 syntax and compatibility
2024-07-18 Made changes to src to match ROS2 standards and syntax
2024-08-09 Deleted unnecessary package dependencies from CMakeLists.tt
2024-09-18 First working version (works until odroid is needed)
2024-11-13 Changes for testing on the odroid
2025-01-20 adding slow vent at beginning
2025-03-04 First complete version in ROS 2
2025-03-10 Adding clarifications and documentations to pneudrive
2025-03-26 Adding documentation and creating more readable code
2025-04-08 Remove tf dependencies because it is never actually used, change wiringpi dependency path for ppa install
2025-04-16 Unified case in the code, fit CMakeLists.txt and package.xml to ROS 2 standard, and added clarifications in the READMEs
2025-05-30 Updating wiringpi heading path
2025-08-23 Add launch file that just does our standard 3 joint arm

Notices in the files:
parts and their libraries:
SparkFun-Boards: Licensing: Creative Commons ShareAlike 4.0 International - https://creativecommons.org/licenses/by-sa/4.0
COPYRIGHT: Copyright (C) 2018 Accelerated Designs. All rights reserved
